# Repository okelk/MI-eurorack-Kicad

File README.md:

This a fork of the Mutable Instruments Eurorack repository.
The original files are all made in EAGLE. Because Autodesk will no longer sell nor support EAGLE effective June 7, 2026 this repository aims to archive them in a more future-proof format for KiCad.

All 'pcb' filders contain subfolders with the original files, versions converted to the older EAGLE v7 format that is needed for the KiCAD import functionality, and Versions in KiCad format.

As of 2026-06-03 those files might not be complete and are untested.
The KiCad importer for EAGLE is quite good but do expect small errors. It looks like all oval holes got lost!

I added [cvpal](https://github.com/pichenettes/cvpal) to this repository for completeness sake, it is not originally part of the MI eurorack repository.

Mutable Instruments' Eurorack Modules.

* [Blades](http://mutable-instruments.net/modules/blades): Dual multimode filter.
* [Blinds](http://mutable-instruments.net/modules/blinds): Quad VC-polarizer.
* [Braids](http://mutable-instruments.net/modules/braids): Macro-oscillator.
* [Branches](http://mutable-instruments.net/modules/branches): Dual Bernoulli gate.
* [Clouds](http://mutable-instruments.net/modules/clouds): Texture synthesizer.
* [Ears](http://mutable-instruments.net/modules/ears): Contact microphone.
* [Edges](http://mutable-instruments.net/modules/edges): Quad chiptune digital oscillator.
* [Elements](http://mutable-instruments.net/modules/elements): Modal synthesizer.
* [Frames](http://mutable-instruments.net/modules/frames): Keyframer/mixer.
* [Grids](http://mutable-instruments.net/modules/grids): Topographic drum sequencer.
* [Kinks](http://mutable-instruments.net/modules/kinks): Utility module - rectifier, analog logic, S&H, noise.
* [Links](http://mutable-instruments.net/modules/links): Utility module - buffer, mixer.
* [Marbles](http://mutable-instruments.net/modules/marbles): Random sampler.
* [Peaks](http://mutable-instruments.net/modules/peaks): Dual trigger converter.
* [Plaits](http://mutable-instruments.net/modules/plaits): Macro oscillator.
* [Rings](http://mutable-instruments.net/modules/rings): Resonator.
* [Ripples](http://mutable-instruments.net/modules/ripples): Liquid 2-pole BP, 2-pole LP and 4-pole LP filter.
* [Shades](http://mutable-instruments.net/modules/shades): Triple attenuverter.
* [Shelves](http://mutable-instruments.net/modules/shelves): EQ filter.
* [Stages](http://mutable-instruments.net/modules/stages): Segment generator.
* [Streams](http://mutable-instruments.net/modules/streams): Dual dynamics gate.
* [Tides](http://mutable-instruments.net/modules/tides): Tidal modulator.
* [Veils](http://mutable-instruments.net/modules/veils): Quad VCA.
* [Volts](http://mutable-instruments.net/modules/volts): +5V power module.
* [Warps](http://mutable-instruments.net/modules/warps): Meta-modulator.
* [Yarns](http://mutable-instruments.net/modules/yarns): MIDI interface.

License
=======

Code (AVR projects): GPL3.0.

Code (STM32F projects): MIT license.

Hardware: cc-by-sa-3.0

By: Emilie Gillet (emilie.o.gillet@gmail.com)

Guidelines for derivative works
===============================

**Mutable Instruments is a registered trademark.**

The name "Mutable Instruments" should not be used on any of the derivative works you create from these files.

We do not recommend you to keep the original name of the Mutable Instruments module for your derivative works.

For example, your 5U adaptation of Mutable Instruments Clouds can be called "Foobar Modular - Particle Generator".

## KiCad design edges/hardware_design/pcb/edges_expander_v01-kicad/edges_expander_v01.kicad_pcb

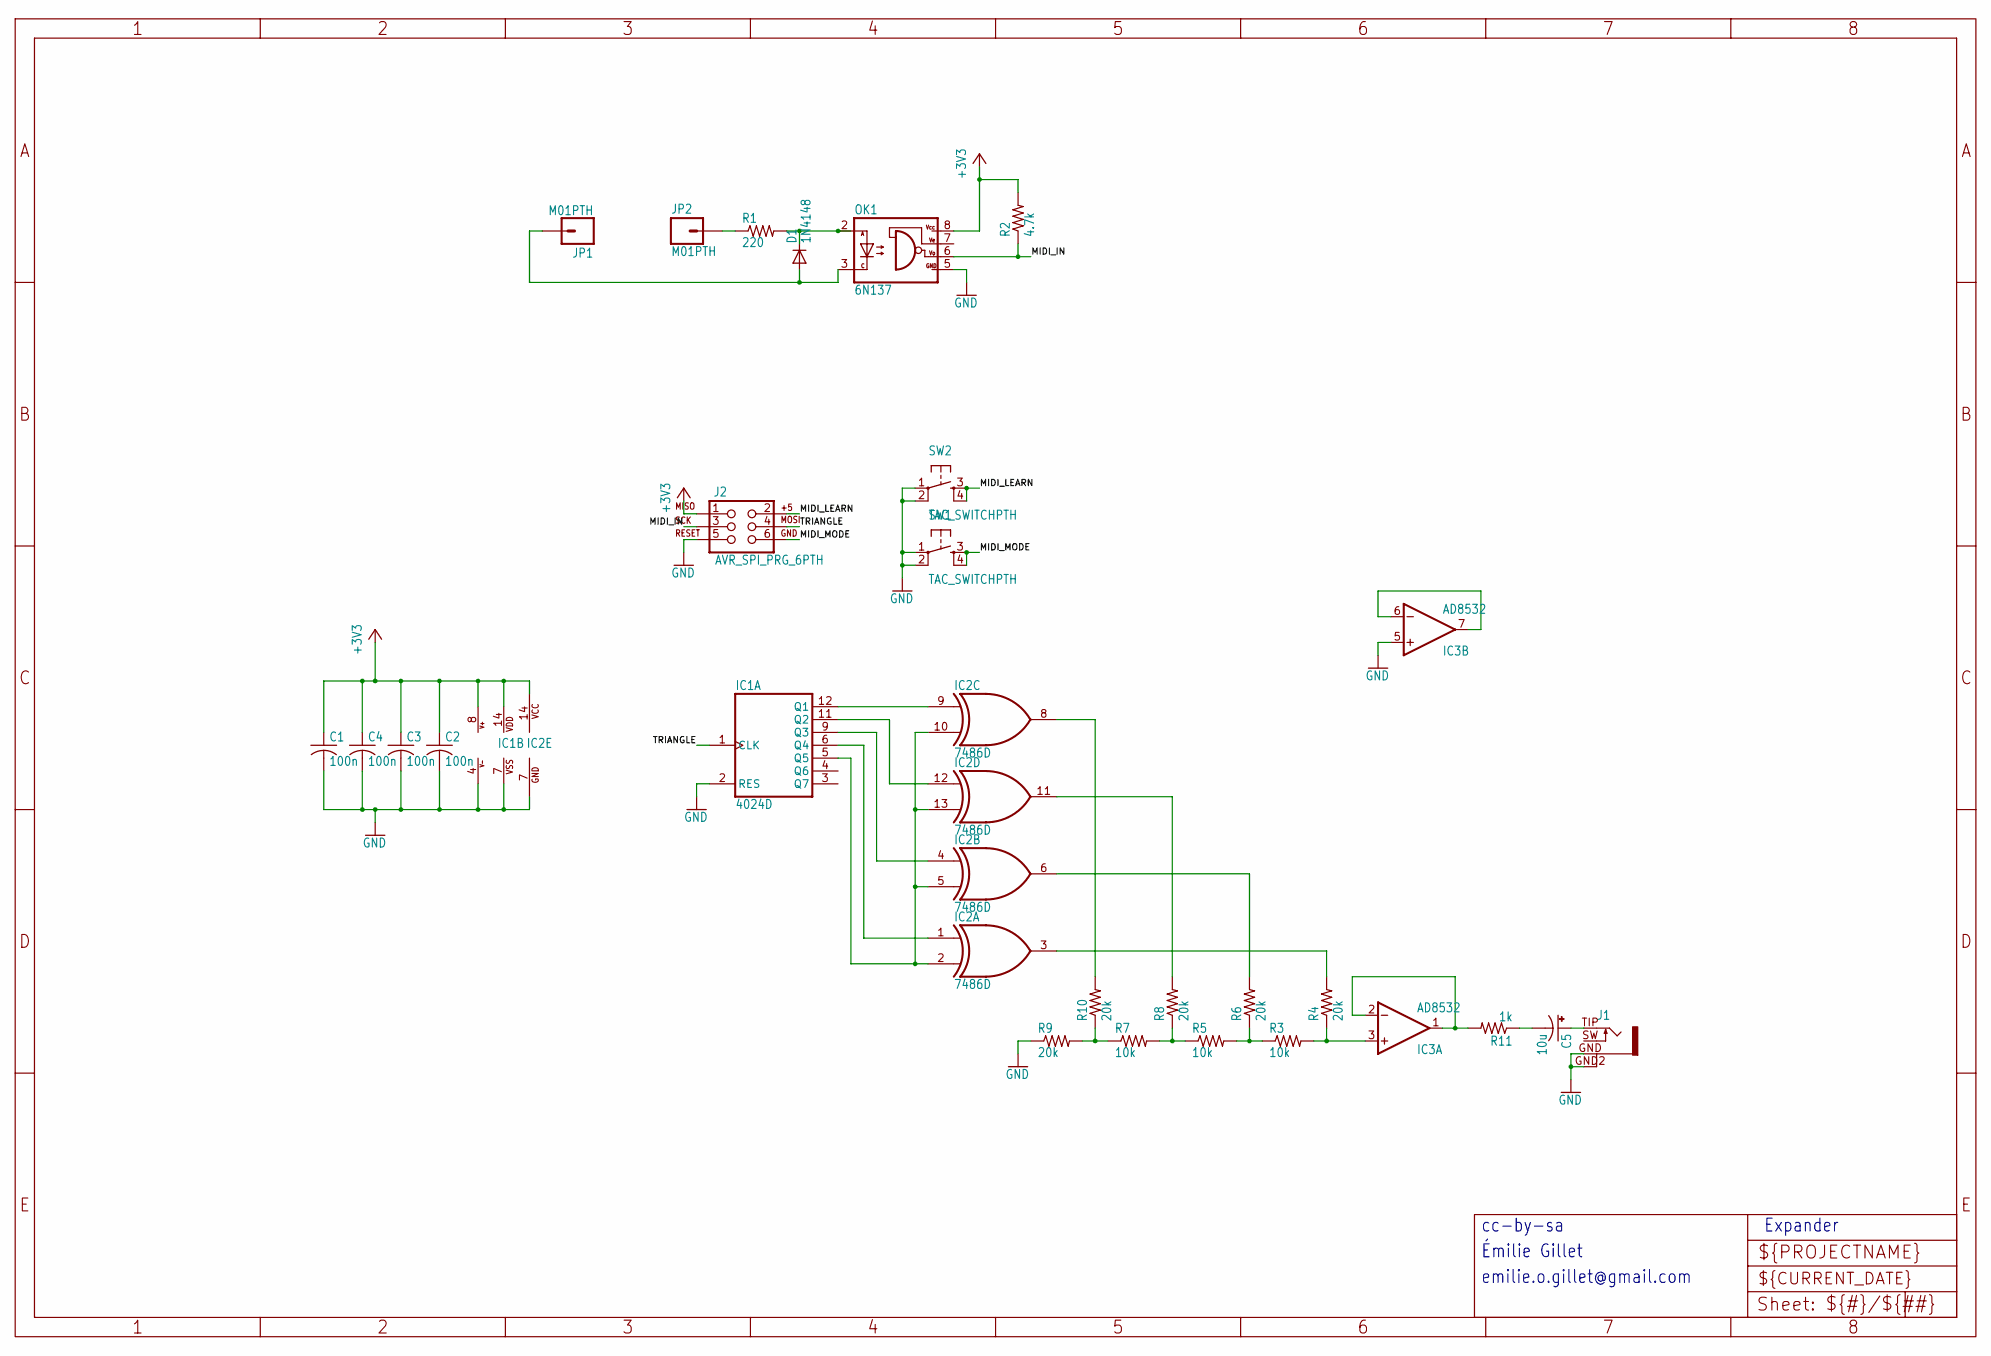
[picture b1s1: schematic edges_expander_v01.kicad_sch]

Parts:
C1, C2, C3, C4: 100n; C0603
C5: 10u; PANASONIC_B
D1: 1N4148; SOD323-W
IC1: 4024D; SO14
IC2: 7486D; SO14
IC3: AD8532; SO08
J1: PJ301WQP; WQP_PJ_301BM
J2: AVR_SPI_PRG_6PTH; 2X3
JP1, JP2: M01PTH; 1X01
OK1: 6N137; DIL8-SMD
R1: 220; R0603
R2: 4.7k; R0603
R3, R5, R7: 10k; R0603
R4, R6, R8, R9, R10: 20k; R0603
R11: 1k; R0603
SW1, SW2: TAC_SWITCHPTH; TACTILE-PTH

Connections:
+3V3_EXP: C1.1, C2.1, C3.1, C4.1, IC1.14 (VDD), IC2.14 (VCC), IC3.8 (V+), J2.1, OK1.8 (VCC), R2.2
GND: C1.2, C2.2, C3.2, C4.2, IC1.2 (RES), IC1.7 (VSS), IC2.7 (GND), IC3.4 (V-), IC3.5 (+IN), J1.GND (1), J1.GND2 (4), J2.5, OK1.5 (GND), R9.1, SW1.1, SW1.2, SW2.1, SW2.2
MIDI_IN: J2.3, OK1.6 (VO), R2.1
MIDI_IN4: JP2.1, R1.1
MIDI_IN5: D1.A, JP1.1, OK1.3 (C)
MIDI_LEARN: J2.2, SW2.3, SW2.4
MIDI_MODE: J2.6, SW1.3, SW1.4
unnamed: IC2.3 (O), R4.2
unnamed: IC2.6 (O), R6.2
unnamed: IC2.11 (O), R8.2
unnamed: IC2.8 (O), R10.2
unnamed: D1.C, OK1.2 (A), R1.2
unnamed: IC1.5 (Q5), IC2.2 (I1), IC2.5 (I1), IC2.10 (I1), IC2.13 (I1)
unnamed: IC1.9 (Q3), IC2.4 (I0)
unnamed: IC1.11 (Q2), IC2.12 (I0)
unnamed: IC1.12 (Q1), IC2.9 (I0)
unnamed: IC3.6 (-IN), IC3.7 (OUT)
unnamed: IC1.6 (Q4), IC2.1 (I0)
unnamed: R7.1, R9.2, R10.1
unnamed: R5.1, R7.2, R8.1
unnamed: R3.1, R5.2, R6.1
unnamed: IC3.3 (+IN), R3.2, R4.1
unnamed: C5.-, R11.1
unnamed: IC3.1 (OUT), IC3.2 (-IN), R11.2
unnamed: C5.+, J1.TIP (2)
TRIANGLE: IC1.1 (CLK), J2.4

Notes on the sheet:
cc-by-sa
emilie.o.gillet@gmail.com
Expander
Émilie Gillet

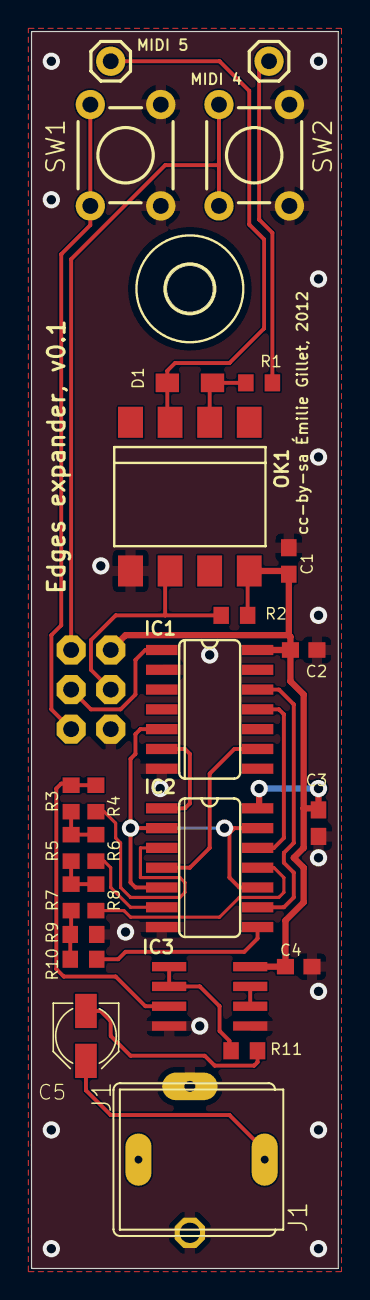
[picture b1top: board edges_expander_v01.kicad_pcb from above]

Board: 2 copper layers, 19.7 x 79.4 mm, 28 parts (1 on the bottom side), 26 nets.

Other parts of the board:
U$1: 3,0

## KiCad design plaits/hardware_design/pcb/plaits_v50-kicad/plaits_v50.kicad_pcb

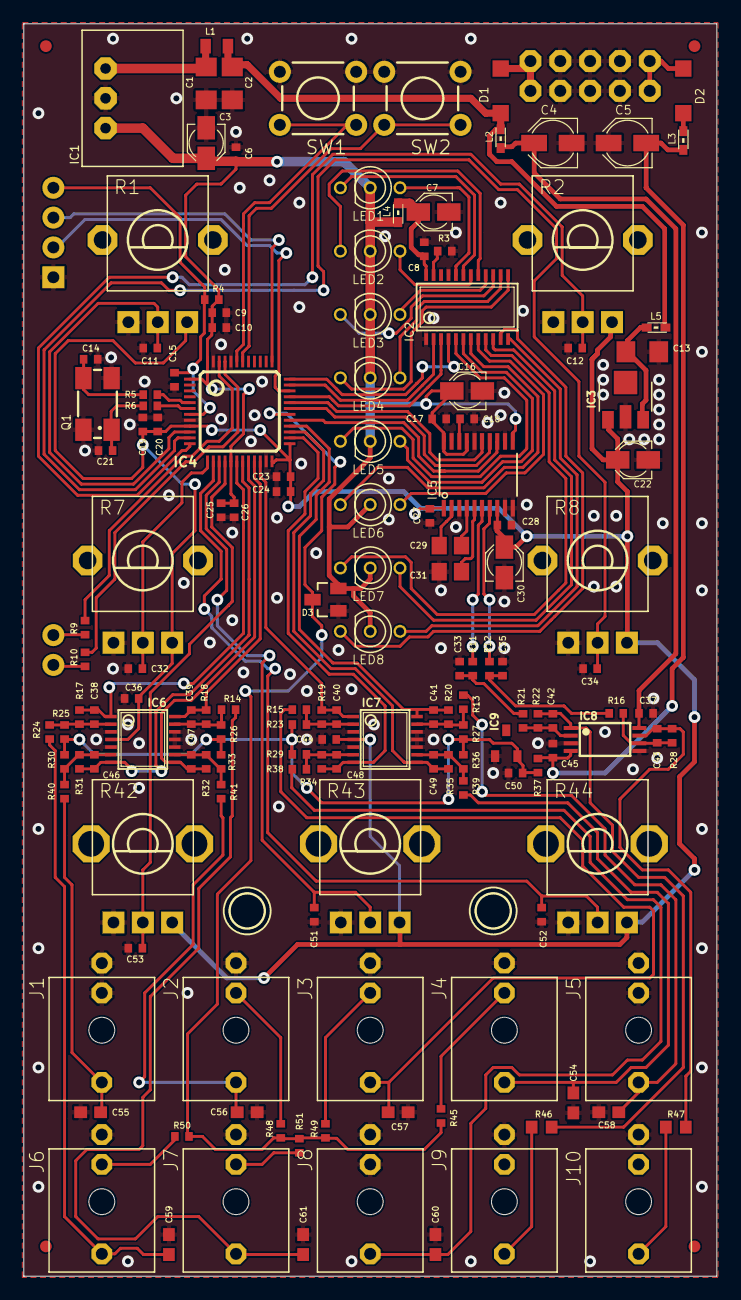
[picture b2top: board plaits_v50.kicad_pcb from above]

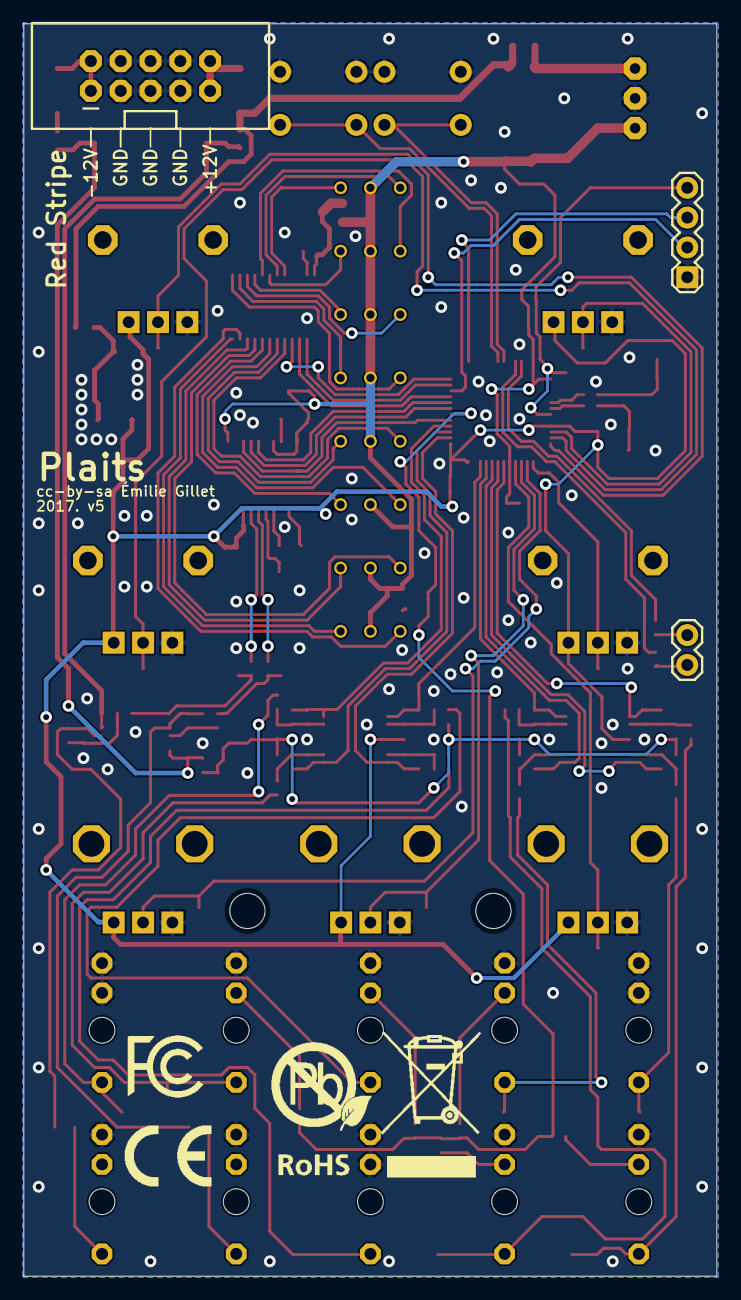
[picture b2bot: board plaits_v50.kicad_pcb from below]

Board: 2 copper layers, 59.0 x 106.7 mm, 162 parts (6 on the bottom side), 100 nets.

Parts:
C1, C2, C13: 22u; C1206
C3, C7, C16, C22, C30: 10u; PANASONIC_A
C4, C5: 22u; PANASONIC_B
C6, C8, C10, C11, C12, C15, C17, C18, C20, C23, C26, C27, C28, C32, C34, C36, C37, C44, C45, C51, C52, C53: 100n; C0402
C9, C19, C24, C25, C50: 1u; C0402
C14, C21: 20p; C0402
C29, C31: 2.2u; C0805
C33, C35, C39, C40, C41, C47, C48, C49: 1.0n; C0402
C38, C42, C43, C46: 100p; C0402
C54, C55, C56, C57, C58, C59, C60, C61: ESD; C0603
D1, D2: 1N5819HW; SOD123
D3: BAT54S; SOT23
H2, H3: MOUNT-HOLE; 3,0TINY
IC1: R-78E3.3-0.5; WE78
IC2: TLC59281DBQ; TSSOP24_0635
IC3: LD2981ABU33; SOT89
IC4: STM32F373CCT6; LQFP48
IC5: PCM5100APW; SSOP20
IC6, IC7: MCP6004; TSSOP14_065
IC8: TL072PW; TSSOP08
IC9: LM4040B10; DBZ_R-PDSO-G3
J1, J2, J3, J4, J5, J6, J7, J8, J9, J10: PJ301_THONKICONN6; WQP_PJ_301M6
JP1, JP2, JP3, JP4: FIDUCIAL1X2; FIDUCIAL-1X2
JP5: 1X02
JP6: 1X04
JP8: M05X2SHD; 2X5-SHROUDED
L1: 33u; L2012C
L2, L3, L4, L5: 0603
LED1, LED2, LED3, LED4, LED5, LED6, LED7, LED8: SSL-LX3059IGW-CA; LED-BICOLOR-THROUGHHOLE-LUMEX
Q1: 8MHz; CTS406
R1, R2, R7, R8: 10kB; ALPS_POT_VERTICAL_PS
R3, R4, R16, R21, R45, R48, R49, R50, R51: 10k; R0402
R5, R6, R9, R10: 100; R0402
R11, R12, R37: 2.2k; R0402
R13, R14, R15, R24, R38, R39, R40, R41: 100k; R0402
R17: 56k; R0402
R18, R20, R22, R28, R31, R34: 33k; R0402
R19, R32, R35: 20k; R0402
R23, R33, R36: 120k; R0402
R25, R27, R30: 200k; R0402
R26: 110k; R0402
R29: 140k; R0402
R42, R43, R44: 10kB; ALPS_POT_VERTICAL
R46, R47: 1.0k; R0603
SW1, SW2: TACTILE-PTH
U$1: FCC_MEDIUM
U$2: ROHS_BIG
U$3: CE_MEDIUM

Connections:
+3V3: C3.+, C6.1, C9.1, C10.1, C16.+, C17.1, C25.1, C26.1, D3.2, IC1.3, IC4.1, IC4.17, IC4.48, IC5.11, IC5.17, IC5.20, L4.2, LED1.A, LED2.A, LED3.A, LED4.A, LED5.A, LED6.A, LED7.A, LED8.A, R4.1
+3V3_A: C19.1, C20.1, C22.+, C23.1, C24.1, C27.1, C28.1, C30.+, C36.1, C44.1, IC3.1, IC4.9, IC4.24, IC4.25, IC5.1, IC5.8, IC6.4, IC7.4, R1.P$1, R2.P$1, R7.P$1, R8.P$1, R42.P$1, R43.P$1, R44.P$1
ADC_FM: C40.2, IC4.22, IC7.1, R19.1
ADC_GATE: C39.2, IC4.21, IC6.14, R18.1
ADC_HARMONICS: C41.2, IC4.28, IC7.14, R20.1
ADC_MODEL: C46.2, IC4.19, IC6.7, R31.1
ADC_MORPH: C49.2, IC4.27, IC7.8, R35.1
ADC_TIMBRE: C47.2, IC4.20, IC6.8, R32.1
ADC_TRIG: C38.2, IC4.18, IC6.1, R17.1
ADC_V_OCT: C48.2, IC4.26, IC7.7, R34.1
AREF_-10: C50.1, IC9.2, R23.2, R25.2, R26.2, R27.2, R29.2, R30.2, R33.2, R36.2, R37.2
DAC_BCK: IC4.29, IC5.13
DAC_DIN: IC4.31, IC5.14
DAC_LRCK: IC4.32, IC5.15
FM_IN: C57.1, J3.P3, R15.2
FREQ_ATT: C51.1, IC4.15, R43.P$2
FREQ_POT: C11.1, IC4.10, R1.P$2
GATE_IN: C61.1, J7.P3, R14.2
GATE_IN1: C59.1, J6.P3, R24.2
GND: C1.2, C2.2, C3.-, C4.-, C5.+, C6.2, C7.-, C8.2, C9.2, C10.2, C11.2, C12.2, C13.2, C14.1, C15.2, C16.-, C17.2, C18.2, C19.2, C20.2, C21.1, C22.-, C23.2, C24.2, C25.2, C26.2, C27.2, C28.2, C30.-, C31.2, C32.2, C33.2, C34.2, C35.2, C36.2, C37.2, C44.2, C45.1, C50.2, C51.2, C52.2, C53.2, C54.2, C55.2, C56.2, C57.2, C58.2, C59.2, C60.2, C61.2, D3.1, IC1.2, IC2.1, IC2.21, IC3.2, IC4.8, IC4.23, IC4.44, IC4.47, IC5.3, IC5.9, IC5.10, IC5.12, IC5.16, IC5.19, IC6.3, IC6.5, IC6.10, IC6.11, IC6.12, IC7.3, IC7.5, IC7.10, IC7.11, IC7.12, IC8.3, IC8.5, IC9.1, J1.P1, J1.P2, J2.P1, J3.P1, J4.P1, J5.P1, J5.P2, J6.P1, J7.P1, J8.P1, J8.P2, J9.P1, J10.P1, JP6.1, JP8.3, JP8.4, JP8.5, JP8.6, JP8.7, JP8.8, Q1.2, Q1.4, R1.P$3, R2.P$3, R3.2, R7.P$3, R8.P$3, R42.P$3, R43.P$3, R44.P$3, SW1.1, SW1.2, SW2.1, SW2.2
HARMONICS_IN: C58.1, J5.P3, R13.2
HARMONICS_POT: C12.1, IC4.12, R2.P$2
LEDS_SCK: IC2.3, IC4.33
LEDS_SIN: IC2.2, IC4.35
LEDS_SS: IC2.4, IC4.36
MODEL_IN: C55.1, J1.P3, R40.2
MORPH_ATT: C52.1, IC4.14, R44.P$2
MORPH_IN: C54.1, J4.P3, R39.2
MORPH_POT: C34.1, IC4.11, R8.P$2
unnamed: C1.1, IC1.1, L1.2
unnamed: IC2.12, LED8.GREEN_C
unnamed: J6.P2, R50.2
unnamed: C38.1, IC6.2, R17.2, R24.1, R25.1
unnamed: IC2.11, LED8.RED_C
unnamed: C29.1, IC5.2
unnamed: IC4.5, R5.1
unnamed: IC4.6, R6.1
unnamed: IC2.10, LED7.GREEN_C
unnamed: IC2.9, LED7.RED_C
unnamed: IC2.8, LED6.GREEN_C
unnamed: IC2.13, LED4.RED_C
unnamed: IC2.7, LED6.RED_C
unnamed: IC2.14, LED4.GREEN_C
unnamed: IC2.6, LED5.GREEN_C
unnamed: C29.2, IC5.4
unnamed: IC2.15, LED3.RED_C
unnamed: IC2.16, LED3.GREEN_C
unnamed: IC2.17, LED2.RED_C
unnamed: IC2.18, LED2.GREEN_C
unnamed: IC2.19, LED1.RED_C
unnamed: IC2.5, LED5.RED_C
unnamed: IC2.20, LED1.GREEN_C
unnamed: J3.P2, R49.1
unnamed: J2.P2, R48.1
unnamed: J4.P2, R45.1
unnamed: C7.+, C8.1, IC2.24, L4.1
unnamed: C39.1, IC6.13, R14.1, R18.2, R26.1
unnamed: C14.2, Q1.3, R5.2
unnamed: C48.1, IC7.6, R29.1, R34.2, R38.1
unnamed: C56.1, J2.P3, R41.2
unnamed: C49.1, IC7.9, R35.2, R36.1, R39.1
unnamed: JP5.2, R10.1
unnamed: C40.1, IC7.2, R15.1, R19.2, R23.1
unnamed: C21.2, Q1.1, R6.2
unnamed: J7.P2, R51.1
unnamed: C46.1, IC6.6, R30.1, R31.2, R40.1
unnamed: D2.A, L3.2
unnamed: C47.1, IC6.9, R32.2, R33.1, R41.1
unnamed: C2.1, D1.C, L1.1, L2.2, L5.2
unnamed: C41.1, IC7.13, R13.1, R20.2, R27.1
unnamed: C13.1, IC3.3, L5.1
unnamed: IC5.6, R11.2
unnamed: C33.1, R11.1, R21.2
unnamed: C35.1, R12.1, R16.2
unnamed: C31.1, IC5.5
unnamed: JP5.1, R9.1
unnamed: C18.1, IC5.18
unnamed: IC5.7, R12.2
unnamed: D1.A, JP8.9, JP8.10
unnamed: C43.1, IC8.6, R16.1, R28.2
unnamed: C43.2, IC8.7, R28.1, R47.2
unnamed: C42.1, IC8.2, R21.1, R22.2
unnamed: C42.2, IC8.1, R22.1, R46.2
unnamed: D2.C, JP8.1, JP8.2
unnamed: J9.P3, R46.1
unnamed: IC2.23, R3.1
unnamed: J10.P3, R47.1
NORMALIZATION_PROBE: D3.3, IC4.30, R45.2, R48.2, R49.2, R50.1, R51.2
RESET: C15.1, IC4.7, JP6.4, R4.2
RX: IC4.46, R9.2
SWCLK: IC4.37, JP6.3
SWDIO: IC4.34, JP6.2
SW_1: IC4.43, SW1.3, SW1.4
SW_2: IC4.42, SW2.3, SW2.4
TIMBRE_ATT: C53.1, IC4.16, R42.P$2
TIMBRE_POT: C32.1, IC4.13, R7.P$2
TX: IC4.45, R10.2
VCC: C4.+, C37.1, IC8.8, L2.1
VEE: C5.-, C45.2, IC8.4, L3.1, R37.1
V_OCT_IN: C60.1, J8.P3, R38.2

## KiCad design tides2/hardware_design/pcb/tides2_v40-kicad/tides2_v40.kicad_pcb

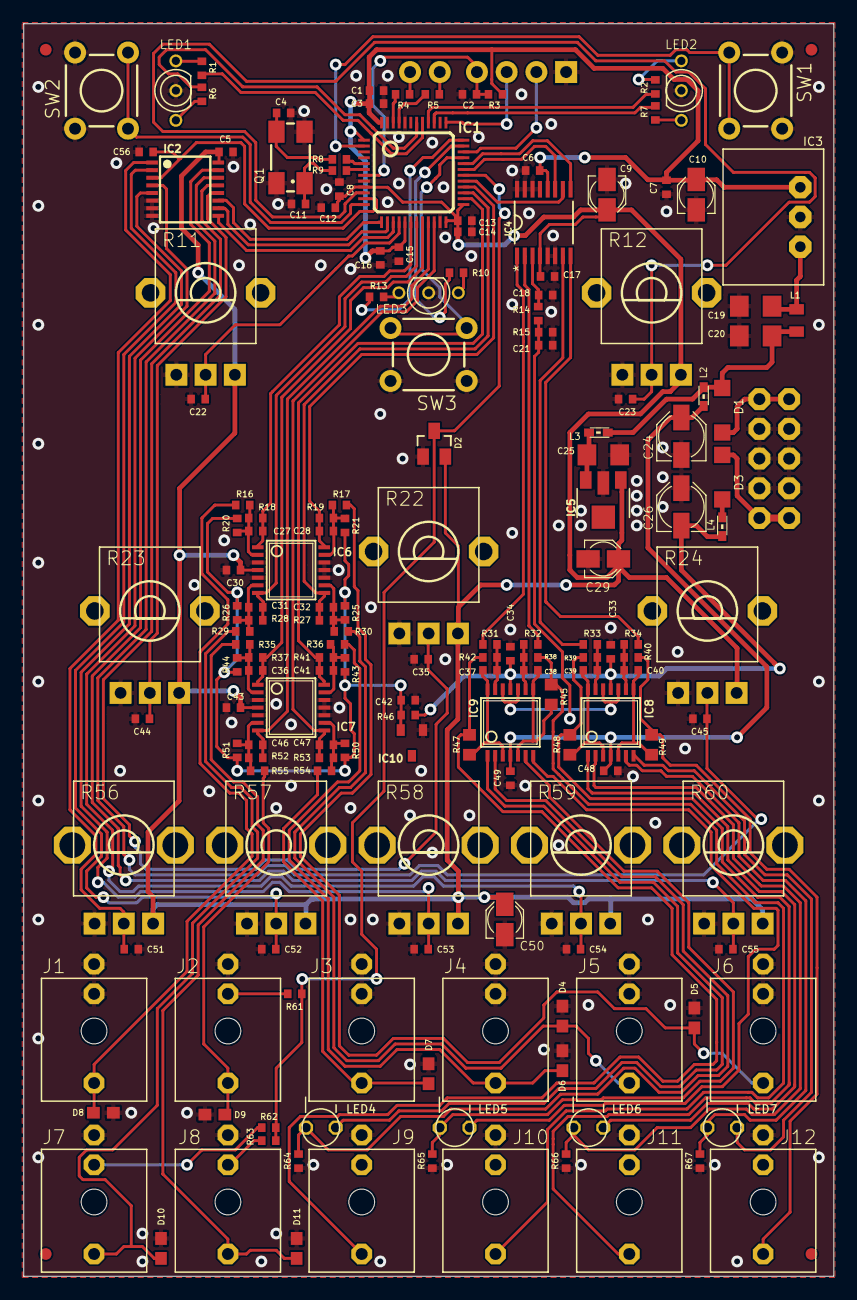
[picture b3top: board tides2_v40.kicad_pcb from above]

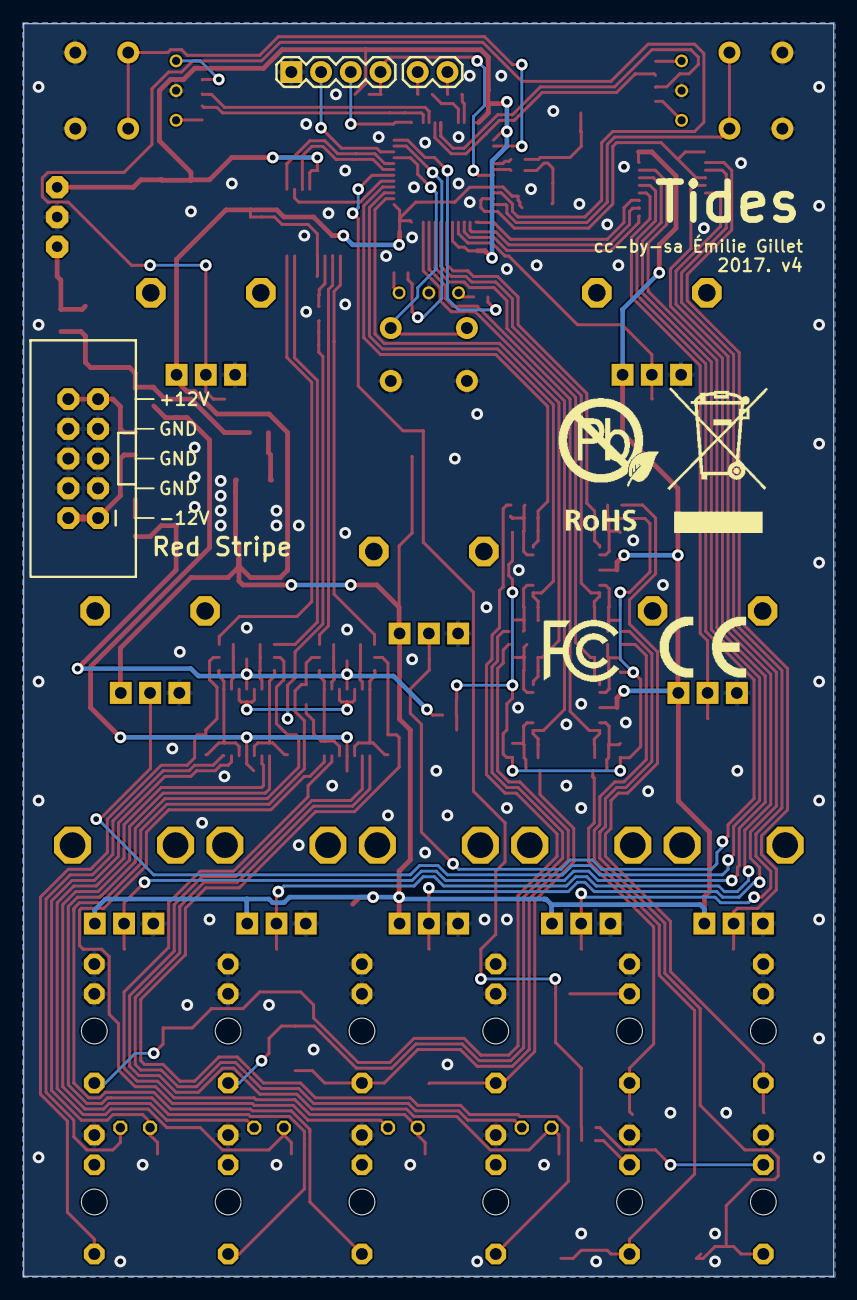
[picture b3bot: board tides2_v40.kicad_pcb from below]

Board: 2 copper layers, 69.2 x 107.0 mm, 181 parts (6 on the bottom side), 109 nets.

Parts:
C1, C12, C13, C16, C18, C21, C42: 1u; C0402
C2, C3, C5, C6, C7, C8, C14, C15, C17, C22, C23, C30, C33, C34, C35, C43, C44, C45, C48, C49, C51, C52, C53, C54, C55: 100n; C0402
C4, C11: 20p; C0402
C9, C10, C29, C50: 10u; PANASONIC_A
C19, C20, C25: 22u; C1206
C24, C26: 22u; PANASONIC_B
C27, C31, C36: 100p; C0402
C28, C32, C41, C46, C47, C56: 1.0n; C0402
C37, C38, C39, C40: 47p; C0402
D1, D3: 1N5819HW; SOD123
D2: BAT54S; SOT23
D4, D5, D6, D7, D8, D9, D10, D11: TVS; 0603
IC1: STM32F373CCT6; LQFP48
IC2: 4051PW; TSSOP16_065
IC3: R-78E3.3-0.5; WE78
IC4: DAC8164ICPW; SOP65P640X110-16N
IC5: LD2981ABU33; SOT89
IC6, IC7: MCP6004; TSSOP14_065
IC8, IC9: TLV4172; TSSOP14_065
IC10: LM4040B10; DBZ_R-PDSO-G3
J1, J2, J3, J4, J5, J6, J7, J8, J9, J10, J11, J12: PJ301_THONKICONN6; WQP_PJ_301M6
JP1, JP2, JP3, JP4: FIDUCIAL1X2; FIDUCIAL-1X2
JP5: M05X2SHD; 2X5-SHROUDED
JP6: 1X04
JP7: 1X02
L1: 33u; L2012C
L2, L3, L4: 0603
LED1, LED2, LED3: W115WSURKMGKW; LED-BICOLOR-THROUGHHOLE-2.54
LED4, LED5, LED6, LED7: 3BC-F; LED3MM
Q1: 8MHz; CTS406
R1, R7, R13: 2.4k; R0402
R2, R6, R10, R46: 1.5k; R0402
R3, R61, R62, R63: 10k; R0402
R4, R5, R8, R9: 100; R0402
R11, R12, R22, R23, R24: 10kB; ALPS_POT_VERTICAL_PS
R14, R28, R37, R38, R39, R40, R42: 130k; R0402
R15, R16, R17, R29, R30, R35, R36, R54, R55: 100k; R0402
R18, R19, R27, R31, R32, R33, R34, R41, R52: 20k; R0402
R20, R21, R25, R43, R51: 120k; R0402
R26, R44: 390k; R0402
R45, R47, R48, R49: 1.0k; R0603
R50: 140k; R0402
R53: 33k; R0402
R56, R57, R58, R59, R60: 10kB; ALPS_POT_VERTICAL
R64, R65, R66, R67: 1.0k; R0402
SW1, SW2, SW3: TACTILE-PTH
U$2: ROHS_BIG
U$4: CE_MEDIUM
U$5: FCC_MEDIUM

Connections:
+3V3: C1.1, C3.1, C6.1, C7.1, C10.+, C15.1, C16.1, IC1.1, IC1.17, IC1.48, IC3.3, IC4.12, R3.1
+3V3_A: C5.1, C8.1, C9.+, C12.1, C13.1, C14.1, C17.1, C29.+, C30.1, C43.1, C50.+, D2.2, IC1.9, IC1.24, IC1.25, IC2.16, IC4.4, IC5.1, IC6.4, IC7.4, R11.P$1, R12.P$1, R22.P$1, R23.P$1, R24.P$1, R56.P$1, R57.P$1, R58.P$1, R59.P$1, R60.P$1
ADC_CLOCK: C36.2, IC1.20, IC7.1, R37.1
ADC_FM: C46.2, IC1.21, IC7.7, R52.1
ADC_SHAPE: C32.2, IC1.27, IC6.8, R27.1
ADC_SHIFT: C28.2, IC1.28, IC6.14, R19.1
ADC_SLOPE: C27.2, IC1.18, IC6.1, R18.1
ADC_SMOOTHNESS: C41.2, IC1.26, IC7.14, R41.1
ADC_TRIG: C31.2, IC1.19, IC6.7, R28.1
ADC_V_OCT: C47.2, IC1.22, IC7.8, R53.1
AREF_-10: C42.1, IC10.2, R20.2, R21.2, R25.2, R26.2, R43.2, R44.2, R46.2, R50.2, R51.2
CLOCK_IN: D11.2, J8.P3, R35.2
DAC_1: IC4.1, R31.2
DAC_2: IC4.2, R32.2
DAC_3: IC4.7, R33.2
DAC_4: IC4.8, R34.2
DAC_MOSI: IC1.31, IC4.11
DAC_SCK: IC1.29, IC4.10
DAC_SS: IC1.32, IC4.9
FM_IN: D9.2, J2.P3, R55.2
FREQUENCY_ATT: C52.1, IC2.2, R57.P$2
FREQUENCY_POT: C22.1, IC1.16, R11.P$2
GND: C1.2, C2.2, C3.2, C4.1, C5.2, C6.2, C7.2, C8.2, C9.-, C10.-, C11.1, C12.2, C13.2, C14.2, C15.2, C16.2, C17.2, C18.2, C19.2, C20.2, C21.2, C22.2, C23.2, C24.-, C25.2, C26.+, C29.-, C30.2, C33.1, C34.1, C35.2, C42.2, C43.2, C44.2, C45.2, C48.2, C49.2, C50.-, C51.2, C52.2, C53.2, C54.2, C55.2, C56.2, D2.1, D4.1, D5.1, D6.1, D7.1, D8.1, D9.1, D10.1, D11.1, IC1.8, IC1.23, IC1.44, IC1.47, IC2.6, IC2.7, IC2.8, IC3.2, IC4.5, IC4.6, IC4.13, IC4.14, IC4.15, IC4.16, IC5.2, IC6.3, IC6.5, IC6.10, IC6.11, IC6.12, IC7.3, IC7.5, IC7.10, IC7.11, IC7.12, IC10.1, J1.P1, J1.P2, J2.P1, J3.P1, J3.P2, J4.P1, J4.P2, J5.P1, J5.P2, J6.P1, J6.P2, J7.P1, J8.P1, J9.P1, J10.P1, J11.P1, J12.P1, JP5.3, JP5.4, JP5.5, JP5.6, JP5.7, JP5.8, JP6.1, LED1.2, LED2.2, LED3.2, Q1.2, Q1.4, R11.P$3, R12.P$3, R15.1, R22.P$3, R23.P$3, R24.P$3, R56.P$3, R57.P$3, R58.P$3, R59.P$3, R60.P$3, R64.2, R65.2, R66.2, R67.2, SW1.1, SW1.2, SW2.1, SW2.2, SW3.1, SW3.2
LED_MODE_G: IC1.35, R10.1
LED_MODE_R: IC1.36, R13.1
LED_RANGE_G: IC1.42, R6.1
LED_RANGE_R: IC1.41, R1.1
LED_SHIFT_G: IC1.40, R2.1
LED_SHIFT_R: IC1.39, R7.1
MUXED_POTS: C56.1, IC1.11, IC2.3
MUX_ADDR_0: IC1.13, IC2.11
MUX_ADDR_1: IC1.14, IC2.10
MUX_ADDR_2: IC1.15, IC2.9
unnamed: C19.1, IC3.1, L1.2
unnamed: J7.P2, R62.1
unnamed: J8.P2, R63.1
unnamed: C27.1, IC6.2, R16.1, R18.2, R20.1
unnamed: IC1.5, R8.1
unnamed: IC1.6, R9.1
unnamed: LED1.3, R1.2
unnamed: LED3.3, R13.2
unnamed: LED3.1, R10.2
unnamed: LED2.3, R7.2
unnamed: LED1.1, R6.2
unnamed: LED2.1, R2.2
unnamed: J2.P2, R61.1
unnamed: C28.1, IC6.13, R17.1, R19.2, R21.1
unnamed: C4.2, Q1.3, R8.2
unnamed: C47.1, IC7.9, R50.1, R53.2, R54.1
unnamed: C46.1, IC7.6, R51.1, R52.2, R55.1
unnamed: JP7.2, R5.1
unnamed: C31.1, IC6.6, R26.1, R28.2, R29.1
unnamed: C11.2, Q1.1, R9.2
unnamed: C32.1, IC6.9, R25.1, R27.2, R30.1
unnamed: D3.A, L4.2
unnamed: C36.1, IC7.2, R35.1, R37.2, R44.1
unnamed: C20.1, D1.C, L1.1, L2.2, L3.2
unnamed: C41.1, IC7.13, R36.1, R41.2, R43.1
unnamed: C25.1, IC5.3, L3.1
unnamed: C37.2, IC9.3, IC9.14, R47.2
unnamed: J11.P3, R39.1, R48.1
unnamed: JP7.1, R4.1
unnamed: J9.P3, R42.1, R47.1
unnamed: C39.1, IC8.13, R33.1, R39.2
unnamed: D1.A, JP5.9, JP5.10
unnamed: J12.P3, R40.1, R49.1
unnamed: C40.1, IC8.9, R34.1, R40.2
unnamed: C38.1, IC9.9, R32.1, R38.2
unnamed: C37.1, IC9.13, R31.1, R42.2
unnamed: J10.P3, R38.1, R45.1
unnamed: D3.C, JP5.1, JP5.2
unnamed: IC9.2, LED4.2, R64.1
unnamed: IC9.1, LED4.1
unnamed: C38.2, IC9.5, IC9.8, R45.2
unnamed: IC9.6, LED5.2, R65.1
unnamed: IC9.7, LED5.1
unnamed: C39.2, IC8.3, IC8.14, R48.2
unnamed: IC8.2, LED6.2, R66.1
unnamed: IC8.1, LED6.1
unnamed: C40.2, IC8.5, IC8.8, R49.2
unnamed: IC8.6, LED7.2, R67.1
unnamed: IC8.7, LED7.1
NORMALIZATION_PROBE: D2.3, IC1.30, R61.2, R62.2, R63.2
RESET: C2.1, IC1.7, JP6.4, R3.2
RX: IC1.46, R4.2
SHAPE_ATT: C54.1, IC2.4, R59.P$2
SHAPE_IN: D4.2, J5.P3, R30.2
SHAPE_POT: C23.1, IC1.10, R12.P$2
SHIFT_ATT: C55.1, IC2.15, R60.P$2
SHIFT_IN: D5.2, J6.P3, R17.2
SHIFT_POT: C45.1, IC2.14, R24.P$2
SLOPE_ATT: C51.1, IC2.1, R56.P$2
SLOPE_IN: D8.2, J1.P3, R16.2
SLOPE_POT: C44.1, IC2.12, R23.P$2
SMOOTHNESS_ATT: C53.1, IC2.5, R58.P$2
SMOOTHNESS_IN: D6.2, J4.P3, R36.2
SMOOTHNESS_POT: C35.1, IC2.13, R22.P$2
SWCLK: IC1.37, JP6.3
SWDIO: IC1.34, JP6.2
SW_MODE: IC1.33, SW3.3, SW3.4
SW_RANGE: IC1.12, SW2.3, SW2.4
SW_SHIFT: IC1.2, SW1.3, SW1.4
TRIG_IN: D10.2, J7.P3, R29.2
TX: IC1.45, R5.2
VCC: C24.+, C48.1, C49.1, IC8.4, IC9.4, L2.1
VEE: C26.-, C33.2, C34.2, IC8.11, IC9.11, L4.1, R46.1
VREF: C18.1, IC4.3, R14.2
VREF_BIAS: C21.1, IC8.10, IC8.12, IC9.10, IC9.12, R14.1, R15.2
V_OCT_IN: D7.2, J3.P3, R54.2

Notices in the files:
edges/hardware_design/pcb/edges_expander_v01-kicad/edges_expander_v01.kicad_pcb:
cc-by-sa Émilie Gillet, 2012
edges/hardware_design/pcb/edges_v20-kicad/edges_v20.kicad_pcb:
cc-by-sa Émilie Gillet, 2014. v2
rings/hardware_design/pcb/rings_v30-kicad/rings_v30.kicad_pcb:
cc-by-sa Émilie Gillet, 2015. v3
streams/hardware_design/pcb/streams_v02_bargraph-kicad/streams_v02_bargraph.kicad_pcb:
cc-by-sa Émilie Gillet, 2014. v0.2
volts/hardware_design/pcb/volts_v01-kicad/volts_v01.kicad_pcb:
cc-by-sa Émilie Gillet. 2013, v0.1
